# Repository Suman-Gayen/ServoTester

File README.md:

# 🔧 Servo Tester PCB Design

A simple and compact **Servo Tester Circuit** designed using **KiCad EDA 9.0.2** for generating PWM signals to test and control standard servo motors.

---

## 📌 Project Overview

This project uses the **NE555 Timer IC** to generate PWM (Pulse Width Modulation) signals required for controlling servo motor position.

By adjusting the potentiometer, the pulse width changes, allowing smooth servo movement and position testing.

---

## 🖼 Project Schematic

```md

```

---

## ⚙ Features

- Servo motor testing
- PWM signal generation
- Adjustable servo position control
- Compact PCB design
- LED power indication
- Simple and beginner-friendly circuit

---

## 🛠 Software Used

| Tool | Version |
|------|---------|
| KiCad EDA | 9.0.2 |

---

## 🔩 Components Used

| Component | Value / Part |
|-----------|--------------|
| U1 | NE555 Timer IC |
| D1 | 1N4148 Diode |
| D2 | LED |
| C1 | 22nF Capacitor |
| R1 | 1KΩ Resistor |
| R2 | 3M3Ω Resistor |
| R3 | 56KΩ Resistor |
| RV1 | 100K Potentiometer |
| J1 | DC Input Connector |
| J2 | Servo Motor Connector |

---

## 🔍 Working Principle

### 1. PWM Signal Generation
The NE555 timer IC generates PWM pulses required for servo motor operation.

### 2. Pulse Width Adjustment
The potentiometer changes the pulse width, which controls the servo angle.

### 3. Servo Control
The generated PWM signal is sent to the servo motor through the signal pin.

### 4. Power Indication
An LED indicator shows the power status of the circuit.

---

## 📐 PCB Design Highlights

- Compact schematic structure
- Beginner-friendly design
- Proper component organization
- Easy PCB routing
- Suitable for learning embedded hardware concepts

---

## 🎯 Learning Outcomes

Through this project, I learned:

- PWM signal generation
- Servo motor interfacing
- NE555 timer configuration
- PCB schematic design in KiCad
- Electronic timing circuit fundamentals

---

## 🚀 Future Improvements

- Add frequency adjustment feature
- Add OLED display for pulse width monitoring
- Add multiple servo output ports
- Design compact single-layer PCB
- Add onboard power regulation

---

## 📂 Project Structure

```bash
Servo-Tester/
│
├── Servo Tester.kicad_sch
├── Servo Tester.kicad_pcb
├── Gerber_Files/
├── Images/
├── BOM/
└── README.md
```

---

## 📸 Recommended Images for Repository

Add these images inside the `images/` folder:

- Schematic Screenshot
- PCB Layout
- 3D PCB View
- Final PCB
- Servo Testing Setup

---

## 🧠 Skills Demonstrated

- PCB Design
- PWM Control
- Servo Interfacing
- KiCad EDA
- Embedded Electronics
- Hardware Development

---

## 👨‍💻 Author

**Suman**  
Electronics & PCB Design Enthusiast

---

## 📜 License

This project is open-source and intended for educational and learning purposes.

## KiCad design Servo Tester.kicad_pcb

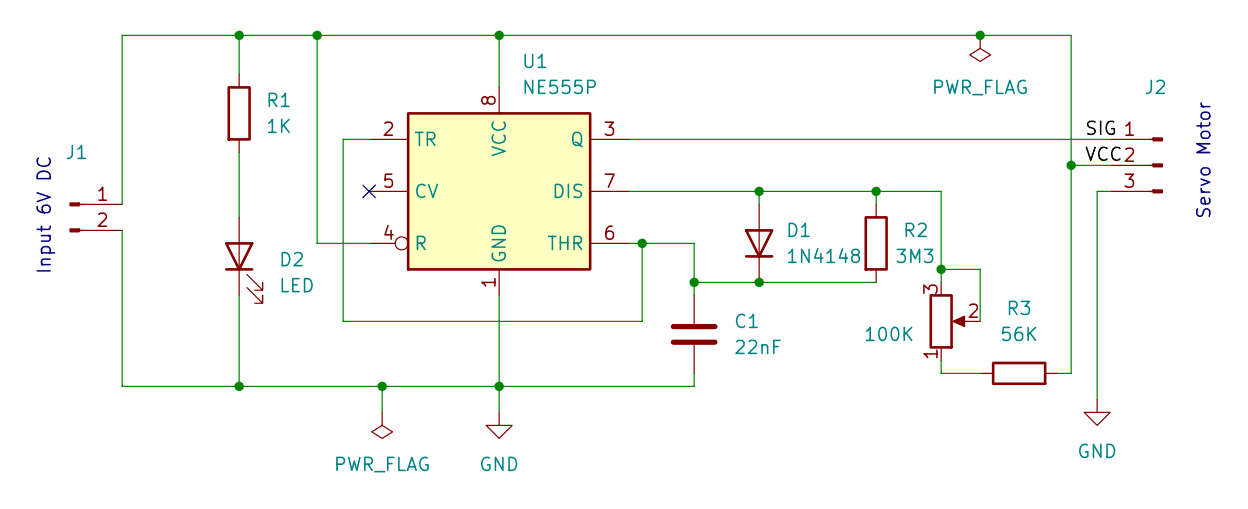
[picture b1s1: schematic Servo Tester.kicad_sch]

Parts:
100K: R_Potentiometer; Potentiometer_Alps_RK163_Single_Horizontal
C1: 22nF; C_Disc_D4.3mm_W1.9mm_P5.00mm
D1: 1N4148; D_DO-35_SOD27_P7.62mm_Horizontal
D2: LED; LED_D3.0mm
J1: Conn_01x02_Pin; PinHeader_1x02_P2.54mm_Horizontal
J2: Conn_01x03_Pin; PinHeader_1x03_P2.54mm_Horizontal
R1: 1K; R_Axial_DIN0207_L6.3mm_D2.5mm_P7.62mm_Horizontal
R2: 3M3; R_Axial_DIN0207_L6.3mm_D2.5mm_P7.62mm_Horizontal
R3: 56K; R_Axial_DIN0207_L6.3mm_D2.5mm_P7.62mm_Horizontal
U1: NE555P; DIP-8_W7.62mm

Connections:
/SIG: J2.1, U1.3 (Q)
/VCC: J1.1, J2.2, R1.1, R3.2, U1.4 (R), U1.8 (VCC)
GND: C1.2, D2.1 (K), J1.2, J2.3, U1.1 (GND)
unnamed: 100K.1, R3.1
unnamed: 100K.2, 100K.3, D1.2 (A), R2.1, U1.7 (DIS)
unnamed: C1.1, D1.1 (K), R2.2, U1.2 (TR), U1.6 (THR)
unnamed: D2.2 (A), R1.2

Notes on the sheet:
Servo Motor
Input 6V DC

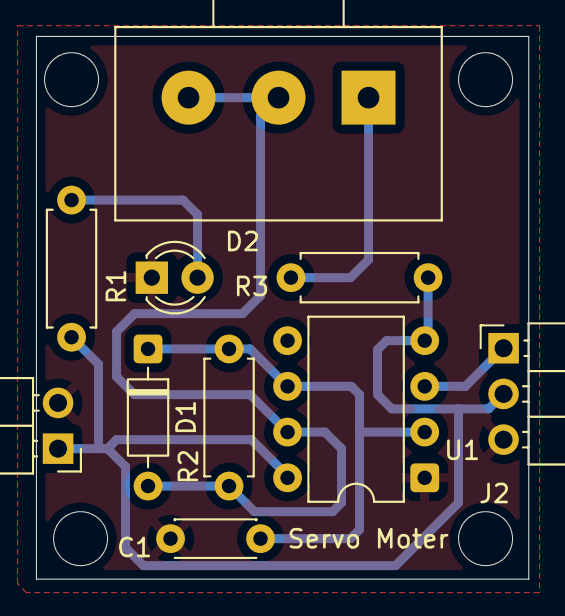
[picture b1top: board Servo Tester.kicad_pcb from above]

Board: 2 copper layers, 27.3 x 30.1 mm, 10 parts (0 on the bottom side), 7 nets.

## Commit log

2026-05-12 servo motor tester
2026-05-17 Revise README for Servo Tester project details
    Updated README to provide detailed project information, features, components, working principles, and future improvements for the Servo Tester PCB design.
